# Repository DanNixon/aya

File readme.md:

# Aya 

Another split keyboard, because the world does not have enough split keyboards.
Very, very inspired by the ErgoDox, but with more keys.

[QMK target](https://github.com/qmk/qmk_firmware/tree/master/keyboards/aya)

## Features

- Split
- Column stagger
- Symmetrical
- Many keys
- (optional combined back plate)
- (optional 3D printable wrist rests)

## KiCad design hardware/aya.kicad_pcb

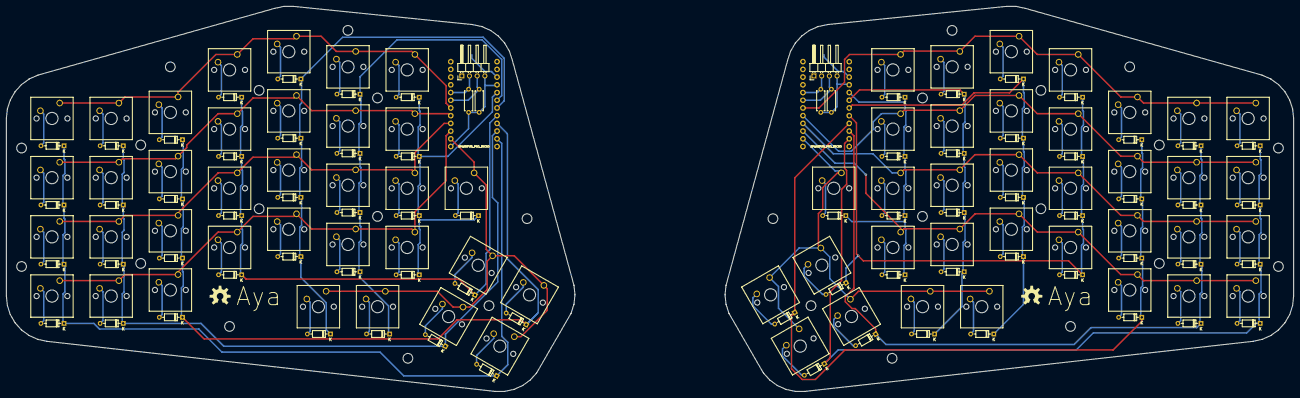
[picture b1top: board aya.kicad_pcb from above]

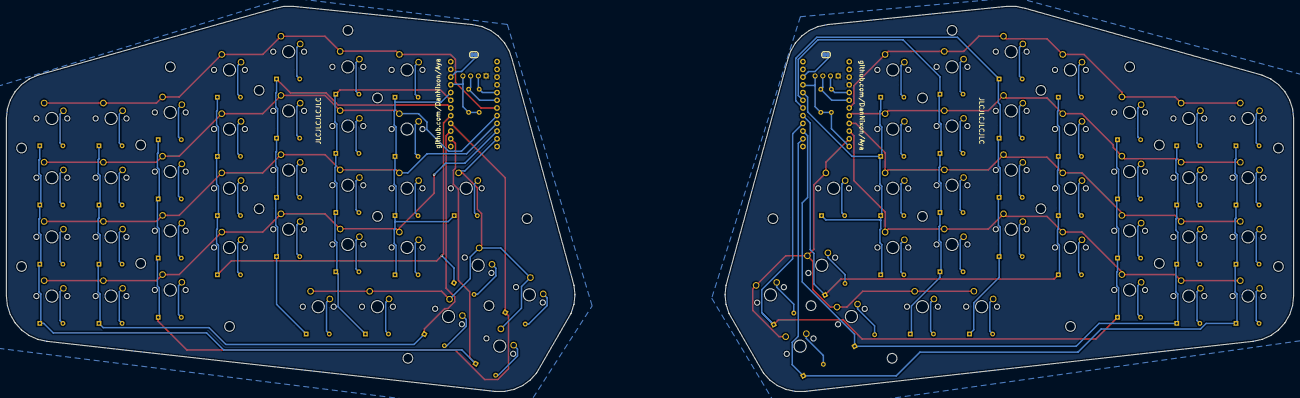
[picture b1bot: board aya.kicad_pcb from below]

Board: 2 copper layers, 424.0 x 126.8 mm, 180 parts (2 on the bottom side), 104 nets.

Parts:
B1, B2: SPARKFUN_PRO_MICRO
D1, D2, D3, D4, D5, D6, D7, D8, D9, D10, D11, D12, D13, D14, D15, D16, D17, D18, D19, D20, D21, D22, D23, D24, D25, D26, D27, D28, D29, D30, D31, D32, D33, D34, D35, D36, D37, D38, D39, D40, D41, D42, D43, D44, D45, D46, D47, D48, D49, D50, D51, D52, D53, D54, D55, D56, D57, D58, D59, D60, D61, D62, D63, D64, D65, D66, D67, D68, D69, D70: D; D_DO-35_SOD27_P7.62mm_Horizontal
HOLE1, HOLE2, HOLE3, HOLE4, HOLE5, HOLE6, HOLE7, HOLE8, HOLE9, HOLE10, HOLE11, HOLE12, HOLE13, HOLE14, HOLE15, HOLE16, HOLE17, HOLE18, HOLE19, HOLE20, HOLE21, HOLE22, HOLE23, HOLE24, HOLE25, HOLE26, HOLE27, HOLE28: MountingHole_3.2mm_M3
J1, J2: CONN_04JST-PTH; PinHeader_1x04_P2.54mm_Horizontal
LOGO1, LOGO2: OSHW-LOGOL; OSHW-LOGO-L
R1, R2, R3, R4: 4K7; R_Axial_DIN0207_L6.3mm_D2.5mm_P7.62mm_Horizontal
SW1, SW36: 11; SW_Cherry_MX_1.00u_PCB
SW2, SW37: 12; SW_Cherry_MX_1.00u_PCB
SW3, SW38: 13; SW_Cherry_MX_1.00u_PCB
SW4, SW39: 14; SW_Cherry_MX_1.00u_PCB
SW5, SW40: 15; SW_Cherry_MX_1.00u_PCB
SW6, SW41: 21; SW_Cherry_MX_1.00u_PCB
SW7, SW42: 22; SW_Cherry_MX_1.00u_PCB
SW8, SW43: 23; SW_Cherry_MX_1.00u_PCB
SW9, SW44: 24; SW_Cherry_MX_1.00u_PCB
SW10, SW45: 25; SW_Cherry_MX_1.00u_PCB
SW11, SW46: 31; SW_Cherry_MX_1.00u_PCB
SW12, SW47: 32; SW_Cherry_MX_1.00u_PCB
SW13, SW48: 33; SW_Cherry_MX_1.00u_PCB
SW14, SW49: 34; SW_Cherry_MX_1.00u_PCB
SW15, SW50: 35; SW_Cherry_MX_1.00u_PCB
SW16, SW51: 41; SW_Cherry_MX_1.00u_PCB
SW17, SW52: 42; SW_Cherry_MX_1.00u_PCB
SW18, SW53: 43; SW_Cherry_MX_1.00u_PCB
SW19, SW54: 44; SW_Cherry_MX_1.00u_PCB
SW20, SW55: 45; SW_Cherry_MX_1.00u_PCB
SW21, SW56: 51; SW_Cherry_MX_1.00u_PCB
SW22, SW57: 52; SW_Cherry_MX_1.00u_PCB
SW23, SW58: 53; SW_Cherry_MX_1.00u_PCB
SW24, SW59: 54; SW_Cherry_MX_1.00u_PCB
SW25, SW60: 55; SW_Cherry_MX_1.00u_PCB
SW26, SW61: 61; SW_Cherry_MX_1.00u_PCB
SW27, SW62: 62; SW_Cherry_MX_1.00u_PCB
SW28, SW63: 63; SW_Cherry_MX_1.00u_PCB
SW29, SW64: 64; SW_Cherry_MX_1.00u_PCB
SW30, SW65: 65; SW_Cherry_MX_1.00u_PCB
SW31, SW66: 71; SW_Cherry_MX_1.00u_PCB
SW32, SW67: 72; SW_Cherry_MX_1.00u_PCB
SW33, SW68: 73; SW_Cherry_MX_1.00u_PCB
SW34, SW69: 74; SW_Cherry_MX_1.00u_PCB
SW35, SW70: 75; SW_Cherry_MX_1.00u_PCB
SW71, SW72: Reset; SolderJumper-2_P1.3mm_Open_RoundedPad1.0x1.5mm

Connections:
/Left Hand Side/C1: B2.20, D36.1, D37.1, D38.1, D39.1, D40.1
/Left Hand Side/C2: B2.19, D41.1, D42.1, D43.1, D44.1, D45.1
/Left Hand Side/C3: B2.18, D46.1, D47.1, D48.1, D49.1, D50.1
/Left Hand Side/C4: B2.17, D51.1, D52.1, D53.1, D54.1, D55.1
/Left Hand Side/C5: B2.16, D56.1, D57.1, D58.1, D59.1, D60.1
/Left Hand Side/C6: B2.15, D61.1, D62.1, D63.1, D64.1, D65.1
/Left Hand Side/C7: B2.14, D66.1, D67.1, D68.1, D69.1, D70.1
/Left Hand Side/GND: B2.3, B2.4, B2.23, J2.1, SW72.2
/Left Hand Side/HAND_SELECT: B2.12, B2.21, J2.4, R3.1, R4.1
/Left Hand Side/R1: B2.7, SW36.1, SW41.1, SW46.1, SW51.1, SW56.1, SW61.1, SW66.1
/Left Hand Side/R2: B2.8, SW37.1, SW42.1, SW47.1, SW52.1, SW57.1, SW62.1, SW67.1
/Left Hand Side/R3: B2.9, SW38.1, SW43.1, SW48.1, SW53.1, SW58.1, SW63.1, SW68.1
/Left Hand Side/R4: B2.10, SW39.1, SW44.1, SW49.1, SW54.1, SW59.1, SW64.1, SW69.1
/Left Hand Side/R5: B2.11, SW40.1, SW45.1, SW50.1, SW55.1, SW60.1, SW65.1, SW70.1
/Left Hand Side/RST: B2.22, SW72.1
/Left Hand Side/SCL: B2.6, J2.3, R3.2
/Left Hand Side/SDA: B2.5, J2.2, R4.2
/Right Hand Side/C1: B1.20, D1.1, D2.1, D3.1, D4.1, D5.1
/Right Hand Side/C2: B1.19, D6.1, D7.1, D8.1, D9.1, D10.1
/Right Hand Side/C3: B1.18, D11.1, D12.1, D13.1, D14.1, D15.1
/Right Hand Side/C4: B1.17, D16.1, D17.1, D18.1, D19.1, D20.1
/Right Hand Side/C5: B1.16, D21.1, D22.1, D23.1, D24.1, D25.1
/Right Hand Side/C6: B1.15, D26.1, D27.1, D28.1, D29.1, D30.1
/Right Hand Side/C7: B1.14, D31.1, D32.1, D33.1, D34.1, D35.1
/Right Hand Side/GND: B1.3, B1.4, B1.12, B1.23, J1.1, SW71.2
/Right Hand Side/R1: B1.7, SW1.1, SW6.1, SW11.1, SW16.1, SW21.1, SW26.1, SW31.1
/Right Hand Side/R2: B1.8, SW2.1, SW7.1, SW12.1, SW17.1, SW22.1, SW27.1, SW32.1
/Right Hand Side/R3: B1.9, SW3.1, SW8.1, SW13.1, SW18.1, SW23.1, SW28.1, SW33.1
/Right Hand Side/R4: B1.10, SW4.1, SW9.1, SW14.1, SW19.1, SW24.1, SW29.1, SW34.1
/Right Hand Side/R5: B1.11, SW5.1, SW10.1, SW15.1, SW20.1, SW25.1, SW30.1, SW35.1
/Right Hand Side/RST: B1.22, SW71.1
/Right Hand Side/SCL: B1.6, J1.3, R1.2
/Right Hand Side/SDA: B1.5, J1.2, R2.2
/Right Hand Side/VCC: B1.21, J1.4, R1.1, R2.1
unnamed: D1.2, SW1.2
unnamed: D2.2, SW2.2
unnamed: D3.2, SW3.2
unnamed: D4.2, SW4.2
unnamed: D5.2, SW5.2
unnamed: D6.2, SW6.2
unnamed: D7.2, SW7.2
unnamed: D8.2, SW8.2
unnamed: D9.2, SW9.2
unnamed: D10.2, SW10.2
unnamed: D11.2, SW11.2
unnamed: D12.2, SW12.2
unnamed: D13.2, SW13.2
unnamed: D14.2, SW14.2
unnamed: D15.2, SW15.2
unnamed: D16.2, SW16.2
unnamed: D17.2, SW17.2
unnamed: D18.2, SW18.2
unnamed: D19.2, SW19.2
unnamed: D20.2, SW20.2
unnamed: D21.2, SW21.2
unnamed: D22.2, SW22.2
unnamed: D23.2, SW23.2
unnamed: D24.2, SW24.2
unnamed: D25.2, SW25.2
unnamed: D26.2, SW26.2
unnamed: D27.2, SW27.2
unnamed: D28.2, SW28.2
unnamed: D29.2, SW29.2
unnamed: D30.2, SW30.2
unnamed: D31.2, SW31.2
unnamed: D32.2, SW32.2
unnamed: D33.2, SW33.2
unnamed: D34.2, SW34.2
unnamed: D35.2, SW35.2
unnamed: D36.2, SW36.2
unnamed: D37.2, SW37.2
unnamed: D38.2, SW38.2
unnamed: D39.2, SW39.2
unnamed: D40.2, SW40.2
unnamed: D41.2, SW41.2
unnamed: D42.2, SW42.2
unnamed: D43.2, SW43.2
unnamed: D44.2, SW44.2
unnamed: D45.2, SW45.2
unnamed: D46.2, SW46.2
unnamed: D47.2, SW47.2
unnamed: D48.2, SW48.2
unnamed: D49.2, SW49.2
unnamed: D50.2, SW50.2
unnamed: D51.2, SW51.2
unnamed: D52.2, SW52.2
unnamed: D53.2, SW53.2
unnamed: D54.2, SW54.2
unnamed: D55.2, SW55.2
unnamed: D56.2, SW56.2
unnamed: D57.2, SW57.2
unnamed: D58.2, SW58.2
unnamed: D59.2, SW59.2
unnamed: D60.2, SW60.2
unnamed: D61.2, SW61.2
unnamed: D62.2, SW62.2
unnamed: D63.2, SW63.2
unnamed: D64.2, SW64.2
unnamed: D65.2, SW65.2
unnamed: D66.2, SW66.2
unnamed: D67.2, SW67.2
unnamed: D68.2, SW68.2
unnamed: D69.2, SW69.2
unnamed: D70.2, SW70.2

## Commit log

2021-04-17 First prototype
2021-04-26 Add 3D printable palm rests
2021-05-08 Add combined lower panel for non-split version
2021-09-10 Photos
2021-12-06 Tidy docs
2021-12-22 Add CI
2022-01-24 Tented case attempt number 1
    Mostly complete, but will probably not be manufactured.
2022-02-13 New tented case design
2022-02-13 Parameterise palm rest height
2022-02-15 Add tabs for base plate
